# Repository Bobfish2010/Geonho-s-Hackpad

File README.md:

# Geonho's Hackpad

First every hackpad project.

# Schematics

# PCBs design

# CAD model

# BOM:

- 1x SEEEDUINO XIAO-RP2040-DIP
- 2x SK6812 MINI LED
- 4x SW_Push
- 1x Case(2 printed parts)
- 4x Blank DSA Keycaps
- 4x M3x16 Bolt
- 4x M3 Heatset
- 1x EC11 rotary encoder

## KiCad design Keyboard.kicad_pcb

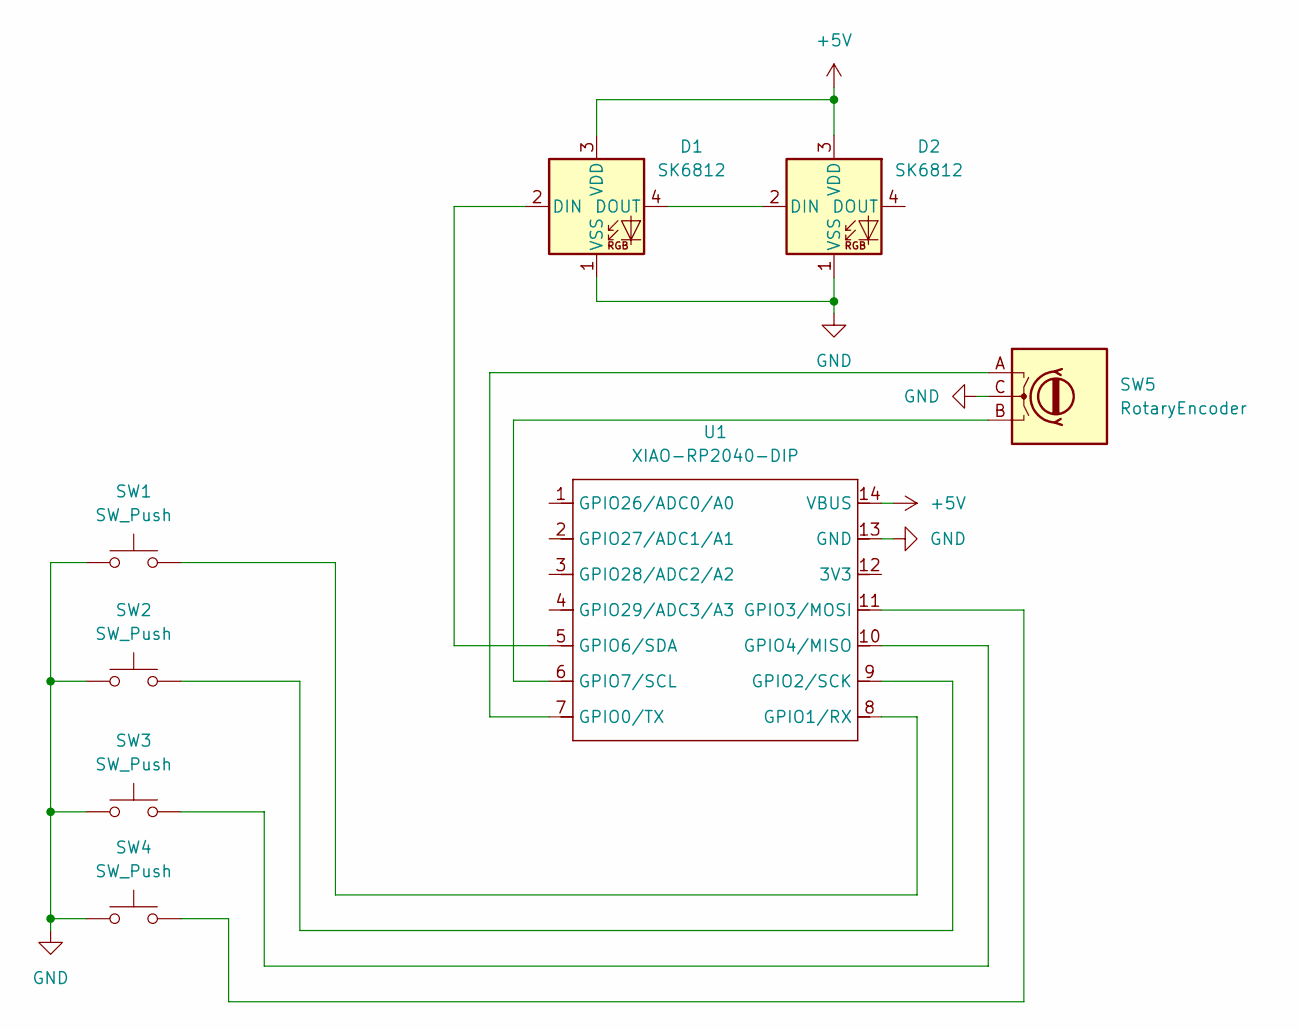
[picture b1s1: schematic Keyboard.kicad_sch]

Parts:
D1, D2: SK6812; LED_SK6812MINI_PLCC4_3.5x3.5mm_P1.75mm
SW1, SW2, SW3, SW4: SW_Push; SW_Cherry_MX_1.00u_PCB
SW5: RotaryEncoder; RotaryEncoder_Alps_EC11E_Vertical_H20mm
U1: XIAO-RP2040-DIP

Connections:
+5V: D1.3 (VDD), D2.3 (VDD), U1.14 (VBUS)
GND: D1.1 (VSS), D2.1 (VSS), SW1.1, SW2.1, SW3.1, SW4.1, SW5.C, U1.13 (GND)
unnamed: D1.2 (DIN), U1.5 (GPIO6/SDA)
unnamed: D1.4 (DOUT), D2.2 (DIN)
unnamed: SW5.A, U1.7 (GPIO0/TX)
unnamed: SW1.2, U1.8 (GPIO1/RX)
unnamed: SW2.2, U1.9 (GPIO2/SCK)
unnamed: SW4.2, U1.11 (GPIO3/MOSI)
unnamed: SW3.2, U1.10 (GPIO4/MISO)
unnamed: SW5.B, U1.6 (GPIO7/SCL)

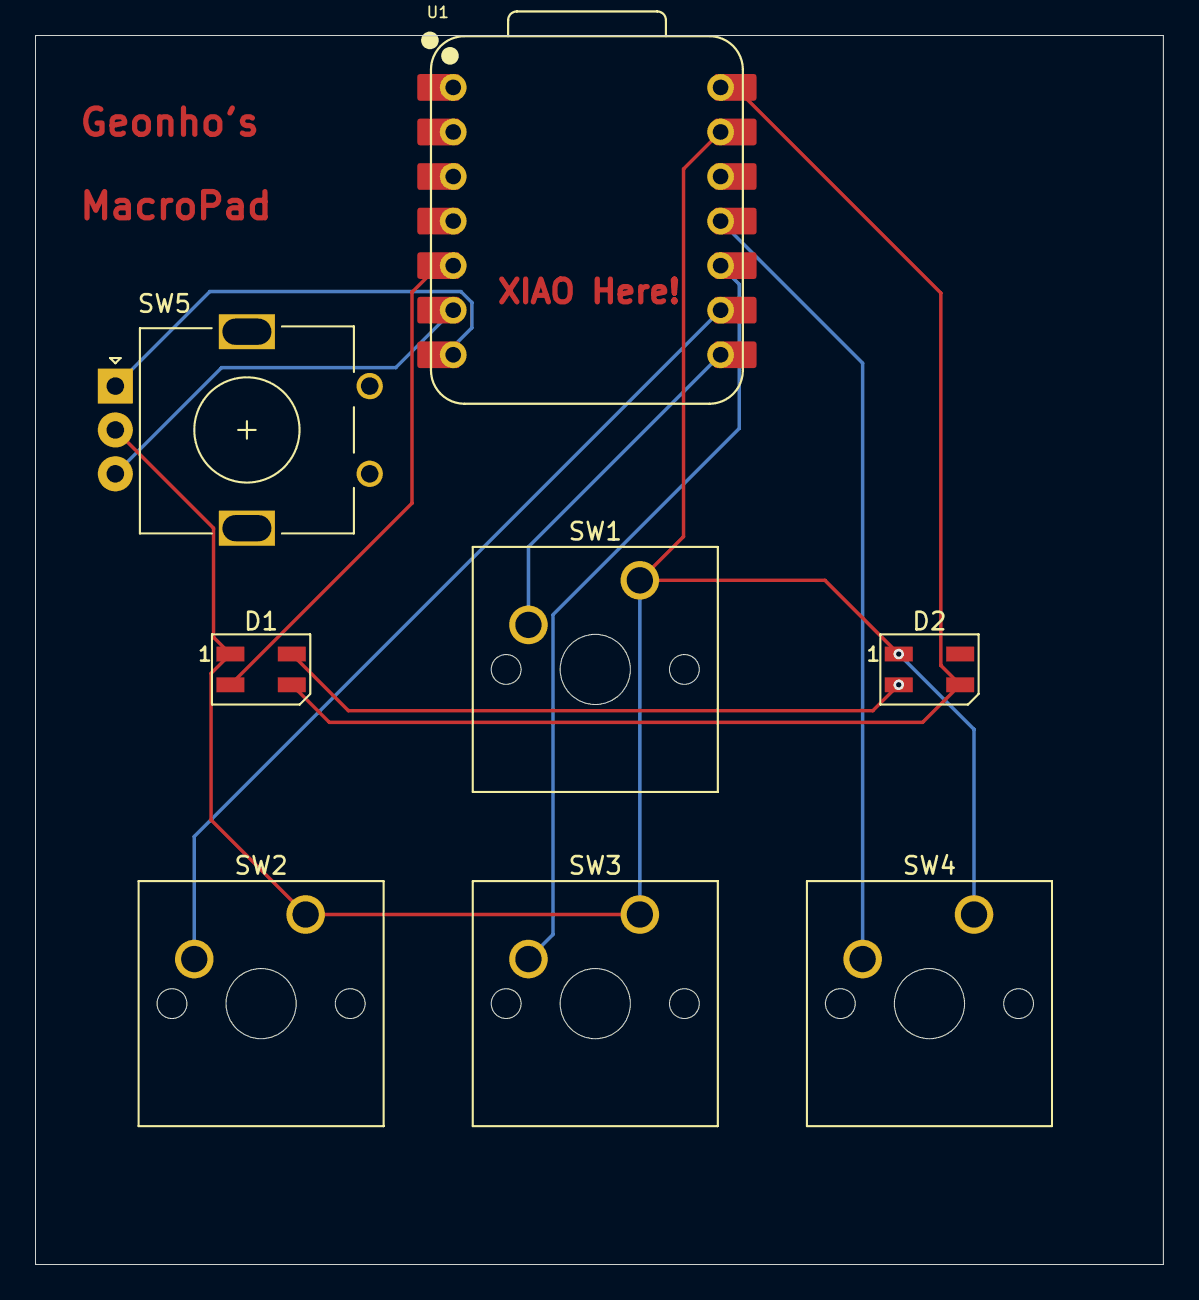
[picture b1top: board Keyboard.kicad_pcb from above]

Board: 2 copper layers, 64.3 x 70.1 mm, 8 parts (0 on the bottom side), 10 nets.

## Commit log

2026-01-18 Rename Keyboard.step to CAD.step
2026-01-18 PCB.step
2026-01-18 Create PCB Blueprint
2026-01-18 Create Syncing Repository
